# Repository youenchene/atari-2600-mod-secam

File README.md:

# Atari 2600 Mod SECAM

This project is documentation and gerber files (files to create PCBs) to get SCART SECAM RGB Video Output of your Atari 2600.

No more blury, awful soup of pixels. Welcome clean big early 80's pixel.

## Disclaimer

All credits remains for Mr Eddy works which you can find here : http://eddystoys.blogspot.com/2014/08/atari-2600.html

If you want a ready to use kit you can buy it here :

- PCB Only : https://klydes-korner.site/en/product/convertisseur-video-rgb-atari-2600-secam-pcb-seul/
- Kit to solder : https://klydes-korner.site/en/product/convertisseur-video-rgb-atari-2600-secam-kit/
- Ready To Use : https://klydes-korner.site/en/product/convertisseur-video-rgb-atari-2600-secam/

You also have  CMS version of the PCB from the Modder Brothers : https://gitlab.com/modderbrothers/a2600-secam-rgb

## Before and After

### Before

### After

## Warning

It need soldering on your Atari 2600, I would say it's medium skill soldering, it's not so difficult.

Be aware you can damage your Atari 2600 and it's your responsability.

## How to build

### PCB

Go to PCBWay, Fast PCB, JL PCB or other supplier using this zip file : [gerber/AtariSecam.zip](gerber/AtariSecam.zip).

If your lazy your use my PCBWay project and make your order from here : https://www.pcbway.com/project/shareproject/Atari_2600_Video_Mod_SECAM_857de2b7.html
## Components

| Reference | Value | Qté |
|---|---|---|
| C1 | 100nF | 1 |
| C2 | 47uF | 1 |
| D1 | D_Zener 2.7v | 1 |
| D2 | D_Zener 10v | 1 |
| R1-R4 | 470R | 4 |
| R5, R10 | 1K | 2 |
| R6 | 1k | 1 |
| R7, R8 | 300R | 2 |
| R9 | 200R | 1 |
| U1 | 74HCT08N | 1 |

You also need :
- a scart cable from garage sales or "Foire à tout" like we say in Normandy.
- wiring cable.

## Wiring

### SCART

| PCB | SCART |
|---|---|
| P9 | SCART R (15) |
| P10 | SCART G (11) |
| P11 | SCART B (7) |
| P12 | SCART Synchro (20) |
| P13 | SCART Com Slow (8) |
| P14 | SCART Com Fast (16) |
| P15 | SCART Audio R (2) |
| P16 | SCART Audio L (6) |
| P17 | SCART Ground R (13) |
| P18 | SCART Ground G (9) |
| P19 | SCART Ground B (5) |
| P20 | SCART Ground Sync (17) |
| P21 | SCART Ground Audio (4) |
| P22 | SCART Shield (21) |

If you get a male/male scart cable that you cut of beware that the wiring between audio (2,4 - 1,5) and synchro (20-19) is inverted (input to output), always check this is the right pin on the scart you will plug. I lost 2 hours to diagnose and rewire.

### Atari 2600

| Mod PCB | Comments | Atari 2600 PCB |
|---|---|---|
| P1 | +5v | Power regulator Right one - green wire on the photo |
| P2 | +9,5v | Power regulator left one - red wire on the photo |
| P3 | Ground | Power regulator middle one - black wire on the photo |
| P4 | TIA LUM 0 | C0111903/UM6521* (Pal) : 7  <br/>  C01014444D (NTSC) : 2 |
| P5 | TIA LUM 1 | C0111903/UM6521* (Pal) : 5 <br/>  C01014444D (NTSC) : 8 |
| P6 | TIA LUM 2 | C0111903/UM6521* (Pal) : 6 <br/>  C01014444D (NTSC) : 5 |
| P7 | TIA Synchro | C0111903/UM6521* (Pal) : 2 <br/>  C01014444D (NTSC) : 7 |
| P8 | TIA Audio | C0111903/UM6521* (Pal) : 13  <br/>  C01014444D (NTSC) : 13 |
| P25 | Iso potential P8 | Not connected |

_Wiring for P1, P2, P3, All credits to Mr Eddy_

To identify better the wiring on the Atari 2600 : 

_All credits to Mr Eddy_

Note that the C011903 can have other name, on mine it was an UM6521P1, it exactly the same wiring as the C011903.

On the table, the C01014444D it's the same chip but for NTSC Atari 2600. 

### LED - Optional

Optional, you can plug a 10mA or 20mA LED on P23 and P24.

P23 is + wiring (long pin).

P24 is ground wiring (short pin).

## Video Tutorials

(French) CabriDIY / [Atari 2600] Construction du kit RGB pour Atari 2600 https://youtu.be/S6Wm6l0JoSQ?si=zYLoU-hGtrezSI1l

(French) CabriDIY / [Atari 2600] Installation d'un mod RGB sur une Atari 2600 (prise péritel) https://youtu.be/MnF89gb17LY?si=qCZCWdnxvj2ZiaQF

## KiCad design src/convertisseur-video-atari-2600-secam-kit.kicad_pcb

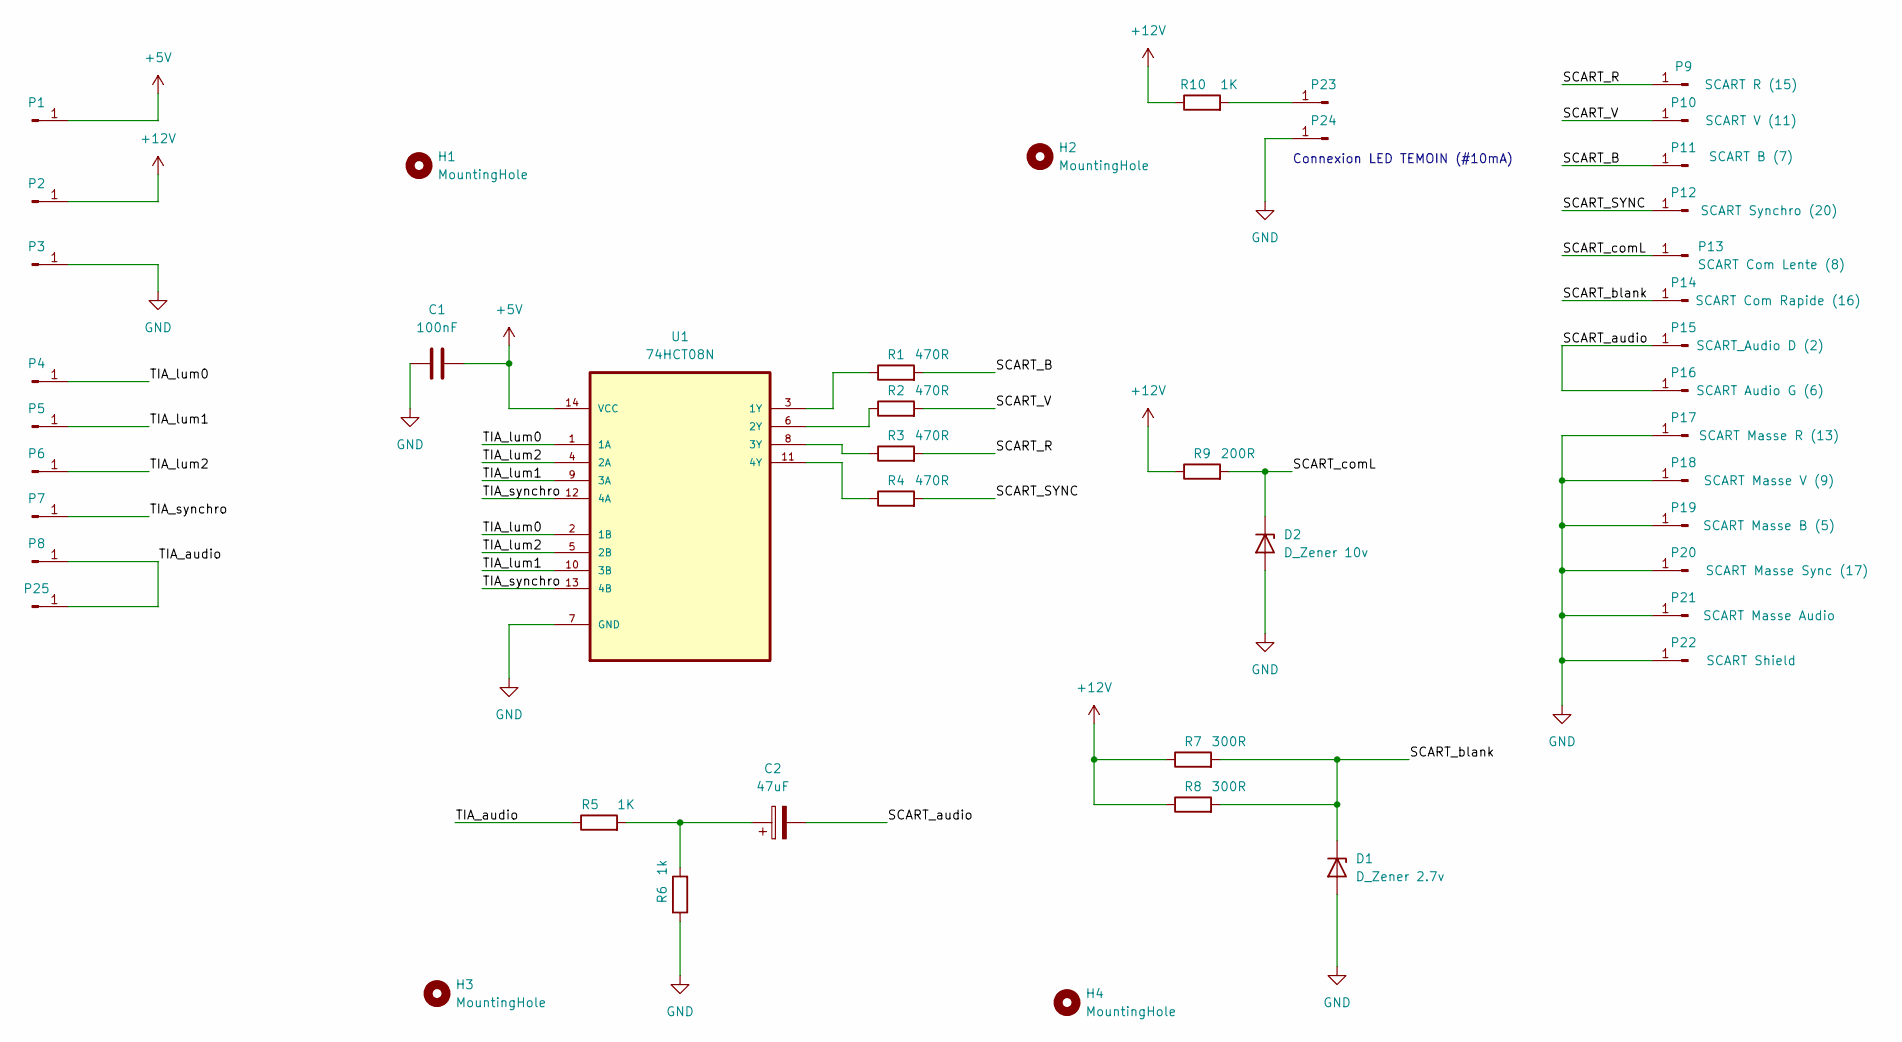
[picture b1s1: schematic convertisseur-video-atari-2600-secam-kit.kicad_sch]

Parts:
C1: 100nF; C_Disc_D4.7mm_W2.5mm_P5.00mm
C2: 47uF; CP_Radial_D6.3mm_P2.50mm
D1: D_Zener 2.7v; D_A-405_P10.16mm_Horizontal
D2: D_Zener 10v; D_A-405_P10.16mm_Horizontal
H1, H2, H3, H4: MountingHole; MountingHole_2.7mm_M2.5_DIN965_Pad
P1, P2, P3, P4, P5, P6, P7, P8, P23, P24, P25: Conn_01x01_Pin; SolderWire-0.5sqmm_1x01_D0.9mm_OD2.1mm
P9: SCART R (15); SolderWire-0.5sqmm_1x01_D0.9mm_OD2.1mm
P10: SCART V (11); SolderWire-0.5sqmm_1x01_D0.9mm_OD2.1mm
P11: SCART B (7); SolderWire-0.5sqmm_1x01_D0.9mm_OD2.1mm
P12: SCART Synchro (20); SolderWire-0.5sqmm_1x01_D0.9mm_OD2.1mm
P13: SCART Com Lente (8); SolderWire-0.5sqmm_1x01_D0.9mm_OD2.1mm
P14: SCART Com Rapide (16); SolderWire-0.5sqmm_1x01_D0.9mm_OD2.1mm
P15: SCART_Audio D (2); SolderWire-0.5sqmm_1x01_D0.9mm_OD2.1mm
P16: SCART Audio G (6); SolderWire-0.5sqmm_1x01_D0.9mm_OD2.1mm
P17: SCART Masse R (13); SolderWire-0.5sqmm_1x01_D0.9mm_OD2.1mm
P18: SCART Masse V (9); SolderWire-0.5sqmm_1x01_D0.9mm_OD2.1mm
P19: SCART Masse B (5); SolderWire-0.5sqmm_1x01_D0.9mm_OD2.1mm
P20: SCART Masse Sync (17); SolderWire-0.5sqmm_1x01_D0.9mm_OD2.1mm
P21: SCART Masse Audio; SolderWire-0.5sqmm_1x01_D0.9mm_OD2.1mm
P22: SCART Shield; SolderWire-0.5sqmm_1x01_D0.9mm_OD2.1mm
R1, R2, R3, R4: 470R; R_Axial_DIN0207_L6.3mm_D2.5mm_P10.16mm_Horizontal
R5, R10: 1K; R_Axial_DIN0207_L6.3mm_D2.5mm_P10.16mm_Horizontal
R6: 1k; R_Axial_DIN0207_L6.3mm_D2.5mm_P10.16mm_Horizontal
R7, R8: 300R; R_Axial_DIN0207_L6.3mm_D2.5mm_P10.16mm_Horizontal
R9: 200R; R_Axial_DIN0207_L6.3mm_D2.5mm_P10.16mm_Horizontal
U1: 74HCT08N; DIP254P762X420-14; MPN 74HCT08N

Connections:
+5V: C1.2, P1.1, U1.14 (VCC)
+12V: P2.1, R7.1, R8.1, R9.1, R10.1
/SCART_B: P11.1, R1.2
/SCART_R: P9.1, R3.2
/SCART_SYNC: P12.1, R4.2
/SCART_V: P10.1, R2.2
/SCART_audio: C2.2, P15.1, P16.1
/SCART_blank: D1.1 (K), P14.1, R7.2, R8.2
/SCART_comL: D2.1 (K), P13.1, R9.2
/TIA_audio: P8.1, P25.1, R5.1
/TIA_lum0: P4.1, U1.1 (1A), U1.2 (1B)
/TIA_lum1: P5.1, U1.9 (3A), U1.10 (3B)
/TIA_lum2: P6.1, U1.4 (2A), U1.5 (2B)
/TIA_synchro: P7.1, U1.12 (4A), U1.13 (4B)
GND: C1.1, D1.2 (A), D2.2 (A), P3.1, P17.1, P18.1, P19.1, P20.1, P21.1, P22.1, P24.1, R6.1, U1.7 (GND)
unnamed: C2.1, R5.2, R6.2
unnamed: P23.1, R10.2
unnamed: R1.1, U1.3 (1Y)
unnamed: R2.1, U1.6 (2Y)
unnamed: R3.1, U1.8 (3Y)
unnamed: R4.1, U1.11 (4Y)

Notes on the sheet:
Connexion LED TEMOIN (#10mA)

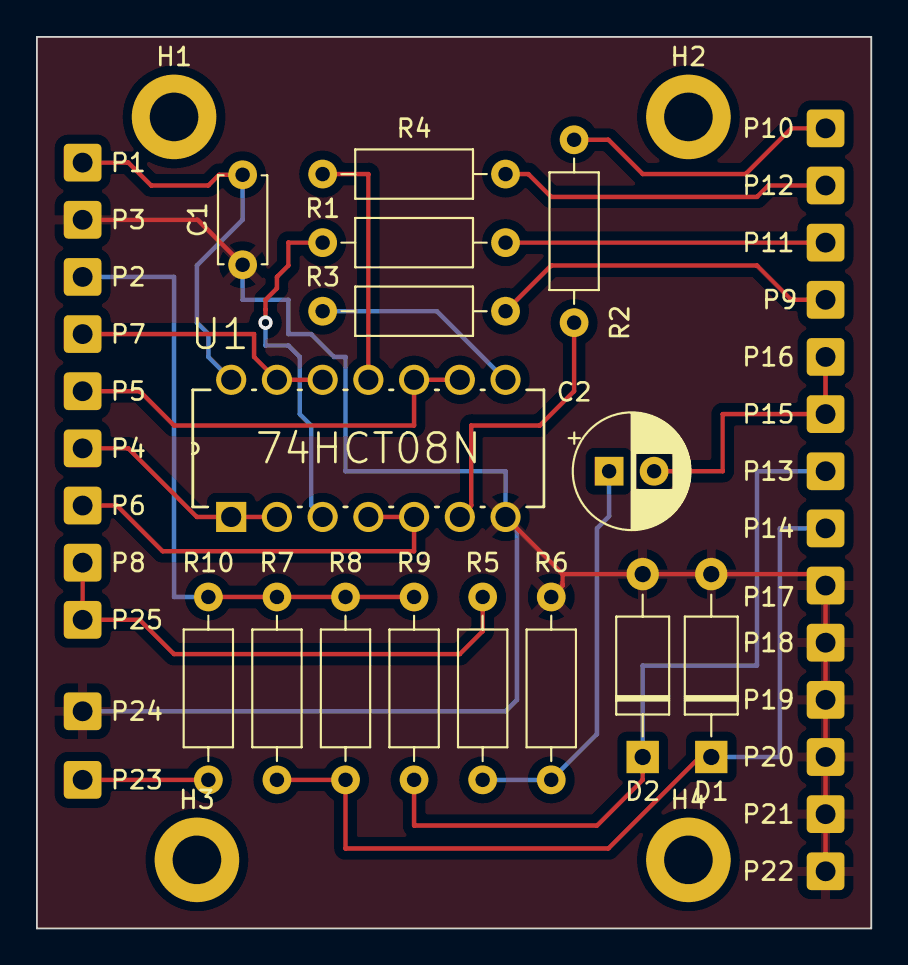
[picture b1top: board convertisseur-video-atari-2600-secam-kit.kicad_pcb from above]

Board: 2 copper layers, 46.4 x 49.5 mm, 44 parts (0 on the bottom side), 21 nets.

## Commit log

2023-11-11 feat: Init commit
2023-11-11 fix: images
2023-11-11 doc: add pcb project link
